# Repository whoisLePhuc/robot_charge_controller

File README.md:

# Robot Charge Controller

An ESP32-based controller for switching, monitoring, and supervising a high-power DC charging path for mobile robots. The project supports two hardware architectures that coexist in this repository and share the same project-local KiCad libraries.

> [!WARNING]
> This project targets a charging path of up to **60 VDC and 20 A**. This energy level can cause arcing, overheating, fire, equipment damage, or personal injury. Both hardware variants are prototypes under development and have not been validated for production or safety-critical use.

## Hardware Variants

| Variant | Description | Current state |
|---|---|---|
| [One-Board Design](hardware/One_Board_Design/README.md) | Relay path, sensing, auxiliary power, ESP32 control, and communications on one PCB | KiCad schematic and PCB present; engineering checks remain open |
| [Split-Board Design](hardware/Split_Board_Design/README.md) | Control Board and Relay Board connected through a controlled interface | Requirements scaffold present; KiCad projects not started |

Both variants are directories in the same repository. Branches are used for temporary changes, not as the only place where a hardware variant can be discovered.

## Design Targets

| Item | Target | Evidence status |
|---|---:|---|
| Main bus voltage | Up to 60 VDC | Project requirement |
| Continuous current | Up to 20 A | Requires electrical and thermal verification |
| Auxiliary input | 24 VDC | Project requirement |
| Controller | ESP32-WROOM-32E | Present in the One-Board Design |
| Communications | CAN, RS485, and 3.3 V UART | Present in the One-Board Design |
| PCB baseline | Two layers, nominal 1.6 mm, 2 oz finished copper on F.Cu and B.Cu | Selected baseline; fabricator stack-up and finish require review |

This project does not replace a battery charger or battery management system. Battery-chemistry charging control, cell balancing, and pack-level protection remain the responsibility of the external charger and BMS.

## Repository Structure

~~~text
robot_charge_controller/
├── README.md
├── CHANGELOG.md
├── LICENSE
├── components/
│   └── bom/                       # BOM workbook candidates and index
├── docs/
│   ├── 01-requirements/
│   ├── 02-architecture/
│   ├── 03-design/
│   ├── 04-calculations/
│   ├── 05-reviews/
│   ├── 06-verification/
│   ├── decisions/                 # Architecture decision records
│   └── workflow.md
├── firmware/
├── hardware/
│   ├── One_Board_Design/
│   ├── Split_Board_Design/
│   ├── libraries/                 # Shared KiCad symbols, footprints, and 3D models
│   └── templates/
├── manufacturing/
├── simulation/
├── test/
└── tools/
~~~

## Getting Started

1. Read the [development workflow](docs/workflow.md).
2. Select a hardware variant from the table above.
3. Review the variant README, requirements, open findings, and shared-library path rules.
4. Open a KiCad project only from its variant directory and keep `hardware/libraries/` in the repository layout.
5. Run the repository organization check:

   ~~~sh
   python tools/check_repository.py
   ~~~

6. Before any hardware gate decision, regenerate ERC/DRC reports and record the exact board revision and open findings.

## Project Evidence

- [BOM candidates](components/bom/README.md)
- [Engineering calculations](docs/04-calculations/README.md)
- [Design guides](docs/03-design/guides/README.md)
- [Architecture decisions](docs/decisions/README.md)
- [Verification records](docs/06-verification/README.md)
- [Manufacturing records](manufacturing/README.md)

## Status

| Area | State |
|---|---|
| Repository baseline | Established; both hardware variants coexist in the repository tree |
| One-Board schematic and PCB | Present; unresolved review actions remain |
| Split-Board requirements | Initial scaffold present |
| Split-Board schematic and PCB | Not started |
| Firmware | Scaffold only |
| Simulation | Scaffold only |
| Prototype verification | Not confirmed by controlled repository evidence |
| Production release | Not authorized |

## License

This repository is licensed under the [MIT License](LICENSE). Component models, third-party libraries, datasheets, and imported engineering artifacts may have separate terms that must be reviewed before redistribution.

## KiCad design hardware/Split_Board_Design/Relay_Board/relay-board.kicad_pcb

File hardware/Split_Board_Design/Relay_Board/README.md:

# Relay Board

This directory is reserved for the relay and high-current PCB of the Split-Board Design.

## Intended Scope

- DC-rated relay and the switched charging-current path.
- High-current connectors and copper paths.
- Local protection, sensing, and relay-drive functions assigned to this board by the architecture decision.
- Test access required for independent power-stage bring-up.

No KiCad project has been created. The board requirements must define normal current, fault current, transient environment, thermal limits, clearances, connectors, safe state, and the [inter-board interface contract](../interface/README.md) before schematic or PCB implementation.

The 60 VDC/20 A values are design requirements, not verified operating capability.

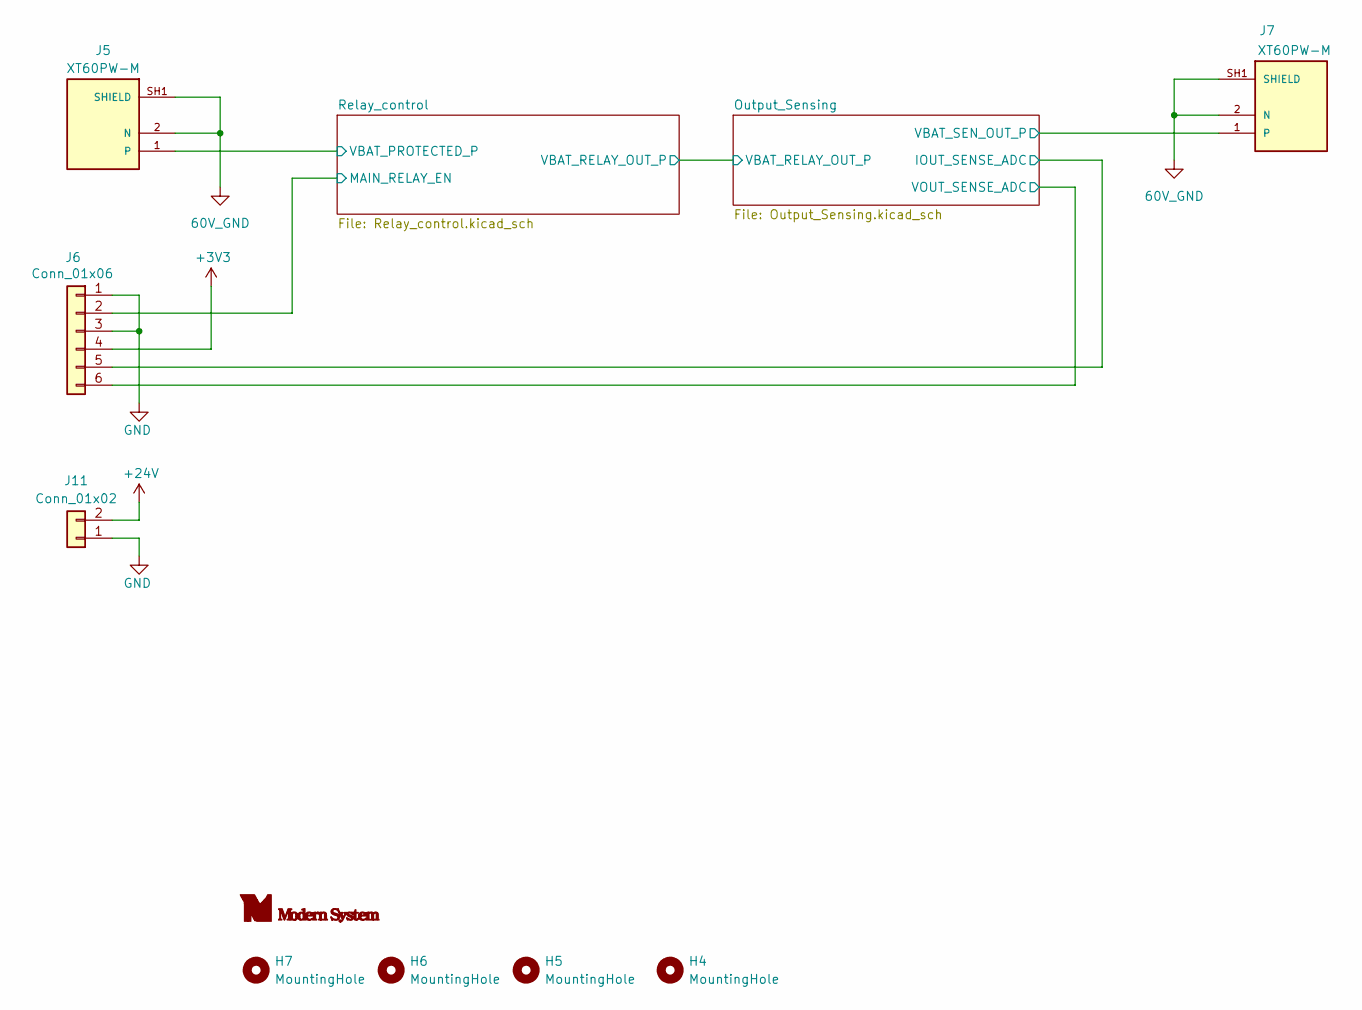
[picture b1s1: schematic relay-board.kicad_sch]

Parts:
H4, H5, H6, H7: MountingHole; MountingHole_3.2mm_M3
J5, J7: XT60PW-M; AMASS_XT60PW-M; PARTREV 1.2
J6: Conn_01x06; JST_XH_S6B-XH-A_1x06_P2.50mm_Horizontal
J11: Conn_01x02; PhoenixContact_MC_1,5_2-G-3.81_1x02_P3.81mm_Horizontal

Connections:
60V_GND: J5.2 (N), J5.SH1 (SHIELD), J5.SH2 (SHIELD), J7.2 (N), J7.SH1 (SHIELD), J7.SH2 (SHIELD); also elsewhere on the board
+3V3: J6.4; also elsewhere on the board
+24V: J11.2; also elsewhere on the board
/Output_Sensing/IOUT_SENSE_ADC: J6.5; also elsewhere on the board
/Output_Sensing/VBAT_SEN_OUT_P: J7.1; also elsewhere on the board
/Output_Sensing/VOUT_SENSE_ADC: J6.6; also elsewhere on the board
/Relay_control/MAIN_RELAY_EN: J6.2; also elsewhere on the board
/Relay_control/VBAT_PROTECTED_P: J5.1; also elsewhere on the board
GND: J6.1, J6.3, J11.1; also elsewhere on the board

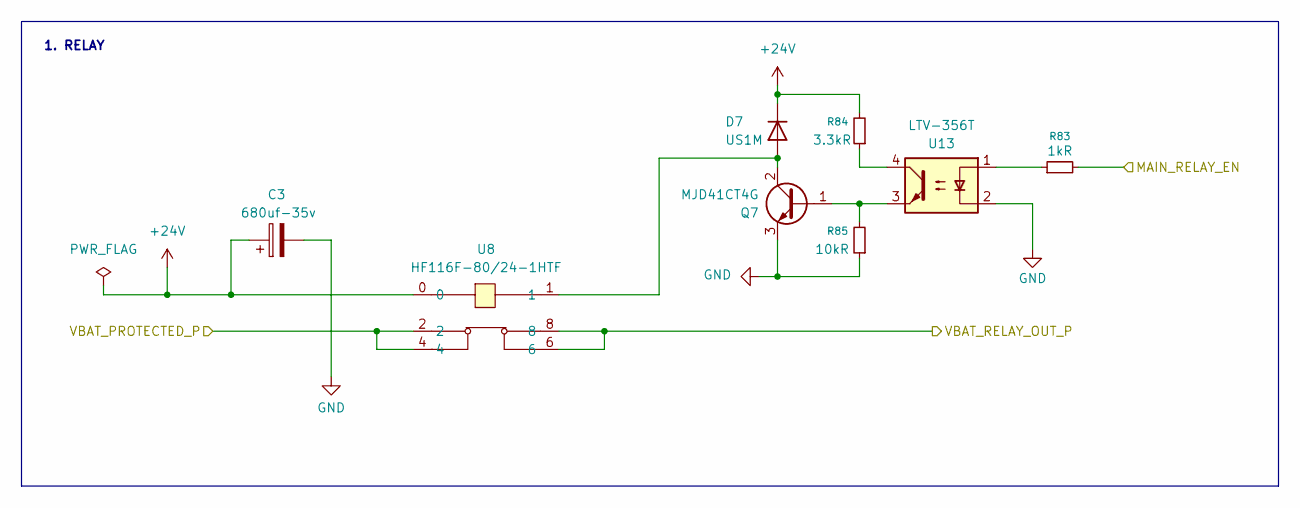
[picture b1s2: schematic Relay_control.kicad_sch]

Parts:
C3: 680uf-35v; CP_Elec_12.5x13.5_Generic_H13
D7: US1M; D_SMA
Q7: MJD41CT4G; TO-252-2
R83: 1kR; R_0805_2012Metric
R84: 3.3kR; R_0805_2012Metric
R85: 10kR; R_0805_2012Metric
U8: HF116F-80/24-1HTF; RELAY-TH_HF116F-80-XX-1HTF
U13: LTV-356T; SO-4_4.4x3.6mm_P2.54mm

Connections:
+24V: C3.1, D7.1 (K), R84.2, U8.0; also elsewhere on the board
/Output_Sensing/VBAT_RELAY_OUT_P: U8.6, U8.8; also elsewhere on the board
/Relay_control/MAIN_RELAY_EN: R83.2; also elsewhere on the board
/Relay_control/VBAT_PROTECTED_P: U8.2, U8.4; also elsewhere on the board
GND: C3.2, Q7.3 (E), R85.1, U13.2; also elsewhere on the board
unnamed: D7.2 (A), Q7.2 (C), U8.1
unnamed: Q7.1 (B), R85.2, U13.3
unnamed: R83.1, U13.1
unnamed: R84.1, U13.4

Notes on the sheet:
1. RELAY

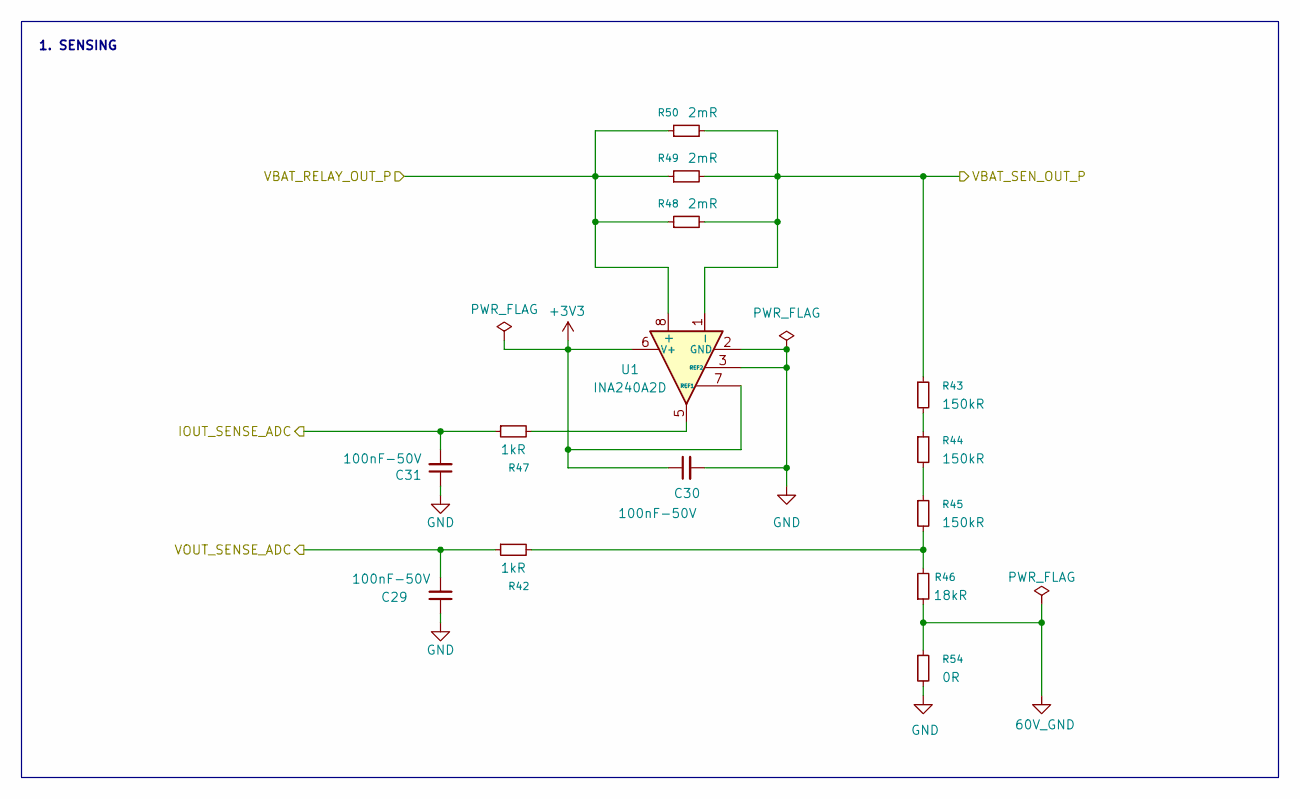
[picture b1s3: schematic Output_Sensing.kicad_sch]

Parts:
C29, C31: 100nF-50V; C_0603_1608Metric
C30: 100nF-50V; C_0805_2012Metric
R42, R47: 1kR; R_0603_1608Metric
R43, R44, R45: 150kR; R_0603_1608Metric
R46: 18kR; R_0603_1608Metric
R48, R49, R50: 2mR; R_Shunt_FOJAN_2512L_4Terminal_Kelvin_C
R54: 0R; R_1206_3216Metric
U1: INA240A2D; SOIC-8_3.9x4.9mm_P1.27mm

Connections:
60V_GND: R46.1, R54.1; also elsewhere on the board
+3V3: C30.1, U1.6 (V+), U1.7 (REF1); also elsewhere on the board
/Output_Sensing/IOUT_SENSE_ADC: C31.2, R47.1; also elsewhere on the board
/Output_Sensing/VBAT_RELAY_OUT_P: R48.1, R49.1, R50.1, U1.8 (+); also elsewhere on the board
/Output_Sensing/VBAT_SEN_OUT_P: R43.1, R48.2, R49.2, R50.2, U1.1 (-); also elsewhere on the board
/Output_Sensing/VOUT_SENSE_ADC: C29.2, R42.1; also elsewhere on the board
GND: C29.1, C30.2, C31.1, R54.2, U1.2 (GND), U1.3 (REF2), U1.4 (GND); also elsewhere on the board
unnamed: R42.2, R45.2, R46.2
unnamed: R43.2, R44.1
unnamed: R44.2, R45.1
unnamed: R47.2, U1.5

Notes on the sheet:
1. SENSING

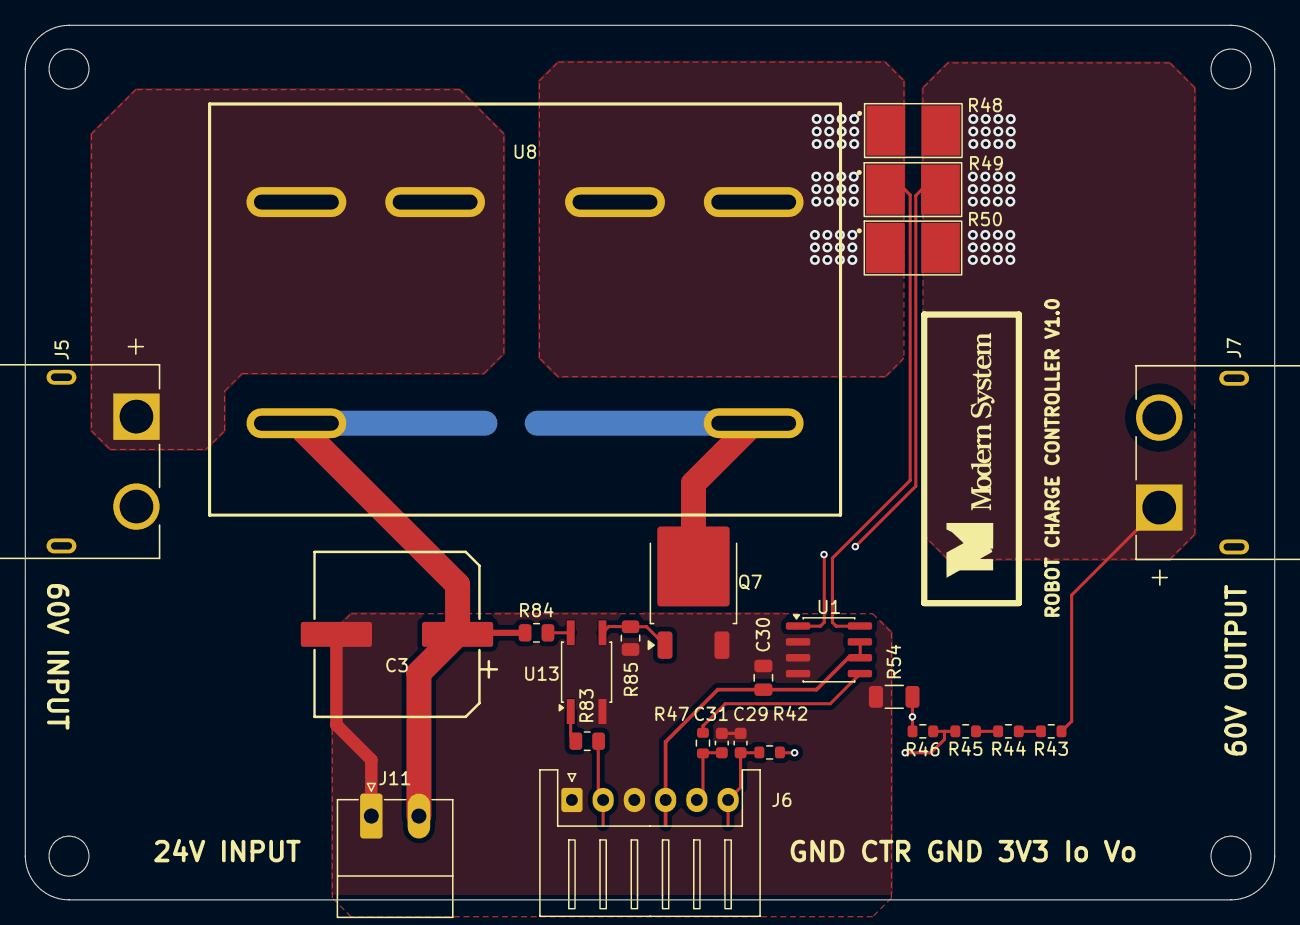
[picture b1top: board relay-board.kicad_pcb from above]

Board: 4 copper layers, 100.0 x 70.0 mm, 30 parts (1 on the bottom side), 18 nets.

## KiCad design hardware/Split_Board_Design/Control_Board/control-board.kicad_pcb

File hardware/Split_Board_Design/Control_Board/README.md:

# Control Board

This directory is reserved for the low-voltage controller PCB of the Split-Board Design.

## Intended Scope

- ESP32 supervision and state control.
- Low-voltage logic power required by the controller electronics.
- USB/programming support and diagnostic access.
- CAN, RS485, and 3.3 V UART communication interfaces.
- External low-voltage inputs and outputs assigned to this board by the interface decision.

No KiCad project has been created. Schematic capture must wait until the [inter-board interface contract](../interface/README.md) defines power, signal, reference-ground, startup, shutdown, and fault behavior.

The final allocation of sensing analog front ends, relay-coil drive, and auxiliary field outputs remains an open architecture decision.

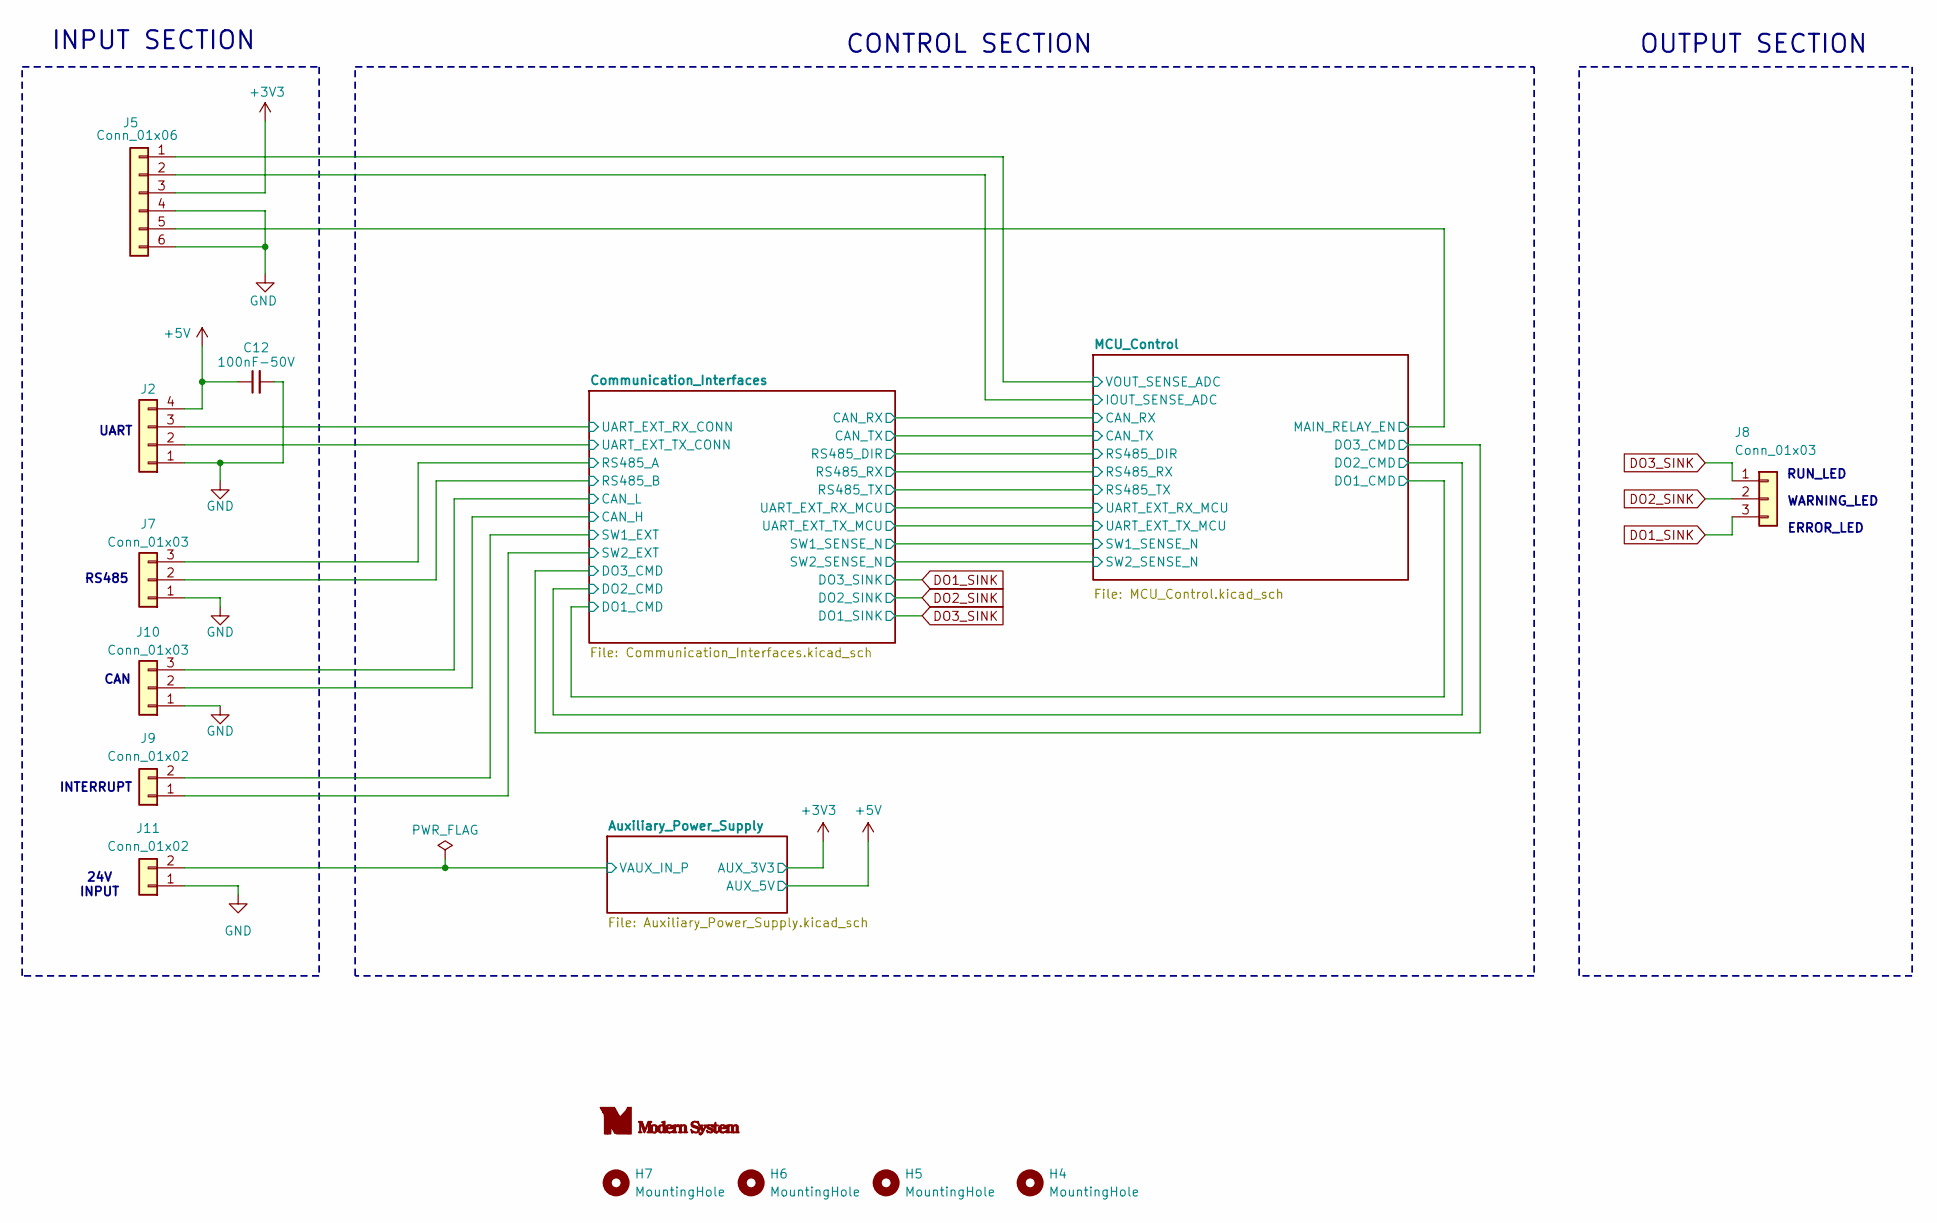
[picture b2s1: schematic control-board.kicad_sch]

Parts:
C12: 100nF-50V; C_0603_1608Metric
H4, H5, H6, H7: MountingHole; MountingHole_3.2mm_M3
J2: UART_CONN; JST_XH_S4B-XH-A-1_1x04_P2.50mm_Horizontal; MPN XH2.54-4P (bent pin)
J5: Conn_01x06; JST_XH_S6B-XH-A_1x06_P2.50mm_Horizontal
J7, J8, J10: Conn_01x03; PhoenixContact_MC_1,5_3-G-3.81_1x03_P3.81mm_Horizontal
J9, J11: Conn_01x02; PhoenixContact_MC_1,5_2-G-3.81_1x02_P3.81mm_Horizontal

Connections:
+3V3: J5.3; also elsewhere on the board
+5V: C12.1, J2.4; also elsewhere on the board
/Auxiliary_Power_Supply/VAUX_IN_P: J11.2; also elsewhere on the board
/Communication_Interfaces/CAN_H: J10.2; also elsewhere on the board
/Communication_Interfaces/CAN_L: J10.3; also elsewhere on the board
/Communication_Interfaces/RS485_A: J7.3; also elsewhere on the board
/Communication_Interfaces/RS485_B: J7.2; also elsewhere on the board
/Communication_Interfaces/SW1_EXT: J9.2; also elsewhere on the board
/Communication_Interfaces/SW2_EXT: J9.1; also elsewhere on the board
/Communication_Interfaces/UART_EXT_RX_CONN: J2.3; also elsewhere on the board
/Communication_Interfaces/UART_EXT_TX_CONN: J2.2; also elsewhere on the board
/MCU_Control/IOUT_SENSE_ADC: J5.2; also elsewhere on the board
/MCU_Control/MAIN_RELAY_EN: J5.5; also elsewhere on the board
/MCU_Control/VOUT_SENSE_ADC: J5.1; also elsewhere on the board
DO1_SINK: J8.3; also elsewhere on the board
DO2_SINK: J8.2; also elsewhere on the board
DO3_SINK: J8.1; also elsewhere on the board
GND: C12.2, J2.1, J5.4, J5.6, J7.1, J10.1, J11.1; also elsewhere on the board

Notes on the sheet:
OUTPUT SECTION
INPUT SECTION
RUN_LED
RS485
WARNING_LED
CONTROL SECTION
INTERRUPT
UART
ERROR_LED
24V INPUT
CAN

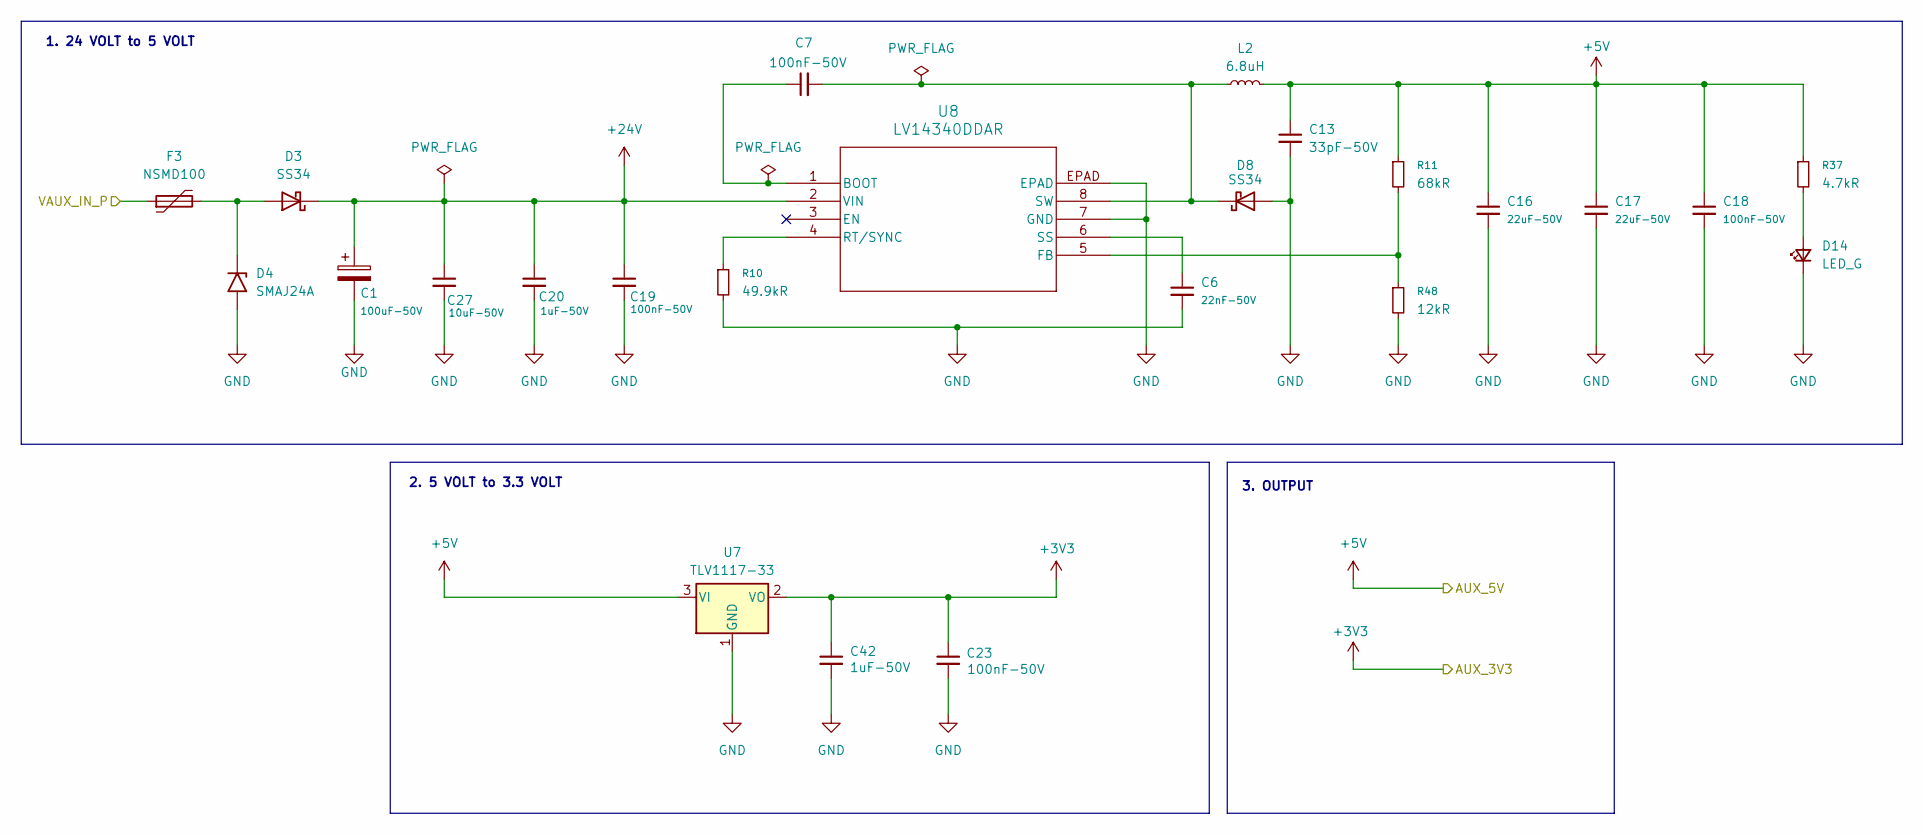
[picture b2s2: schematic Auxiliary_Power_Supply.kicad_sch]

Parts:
C1: 100uF-50V; CP_Elec_8x10.5
C6: 22nF-50V; C_0603_1608Metric
C7, C18, C19, C23: 100nF-50V; C_0603_1608Metric
C13: 33pF-50V; C_0603_1608Metric
C16, C17: 22uF-50V; C_0805_2012Metric
C20, C42: 1uF-50V; C_0603_1608Metric
C27: 10uF-50V; C_0603_1608Metric
D3, D8: SS34; D_SMA; LCSC Part C2837271
D4: SMAJ24A; D_SMA
D14: LED_G; LED_0603_1608Metric
F3: NSMD100; Fuse_1206_3216Metric; MPN nSMD100; LCSC Part C66453
L2: 6.8uH; L_Changjiang_FXL0630
R10: 49.9kR; R_0603_1608Metric
R11: 68kR; R_0603_1608Metric
R37: 4.7kR; R_0603_1608Metric
R48: 12kR; R_0603_1608Metric
U7: TLV1117-33; SOT-223-3_TabPin2
U8: LV14340DDAR; SOIC8_DDA_TEX

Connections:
+3V3: C23.1, C42.1, U7.2 (VO); also elsewhere on the board
+5V: C13.1, C16.1, C17.1, C18.1, L2.2, R11.1, R37.1, U7.3 (VI); also elsewhere on the board
+24V: C1.1, C19.1, C20.1, C27.1, D3.1 (K), U8.2 (VIN); also elsewhere on the board
/Auxiliary_Power_Supply/VAUX_IN_P: F3.1; also elsewhere on the board
GND: C1.2, C6.2, C13.2, C16.2, C17.2, C18.2, C19.2, C20.2, C23.2, C27.2, C42.2, D4.2 (A2), D8.2 (A), D14.1 (K), R10.2, R48.2, U7.1 (GND), U8.7 (GND), U8.EPAD; also elsewhere on the board
unnamed: D3.2 (A), D4.1 (A1), F3.2
unnamed: C7.2, D8.1 (K), L2.1, U8.8 (SW)
unnamed: D14.2 (A), R37.2
unnamed: C7.1, U8.1 (BOOT)
unnamed: R11.2, R48.1, U8.5 (FB)
unnamed: R10.1, U8.4 (RT/SYNC)
unnamed: C6.1, U8.6 (SS)

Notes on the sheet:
2. 5 VOLT to 3.3 VOLT
1. 24 VOLT to 5 VOLT
3. OUTPUT

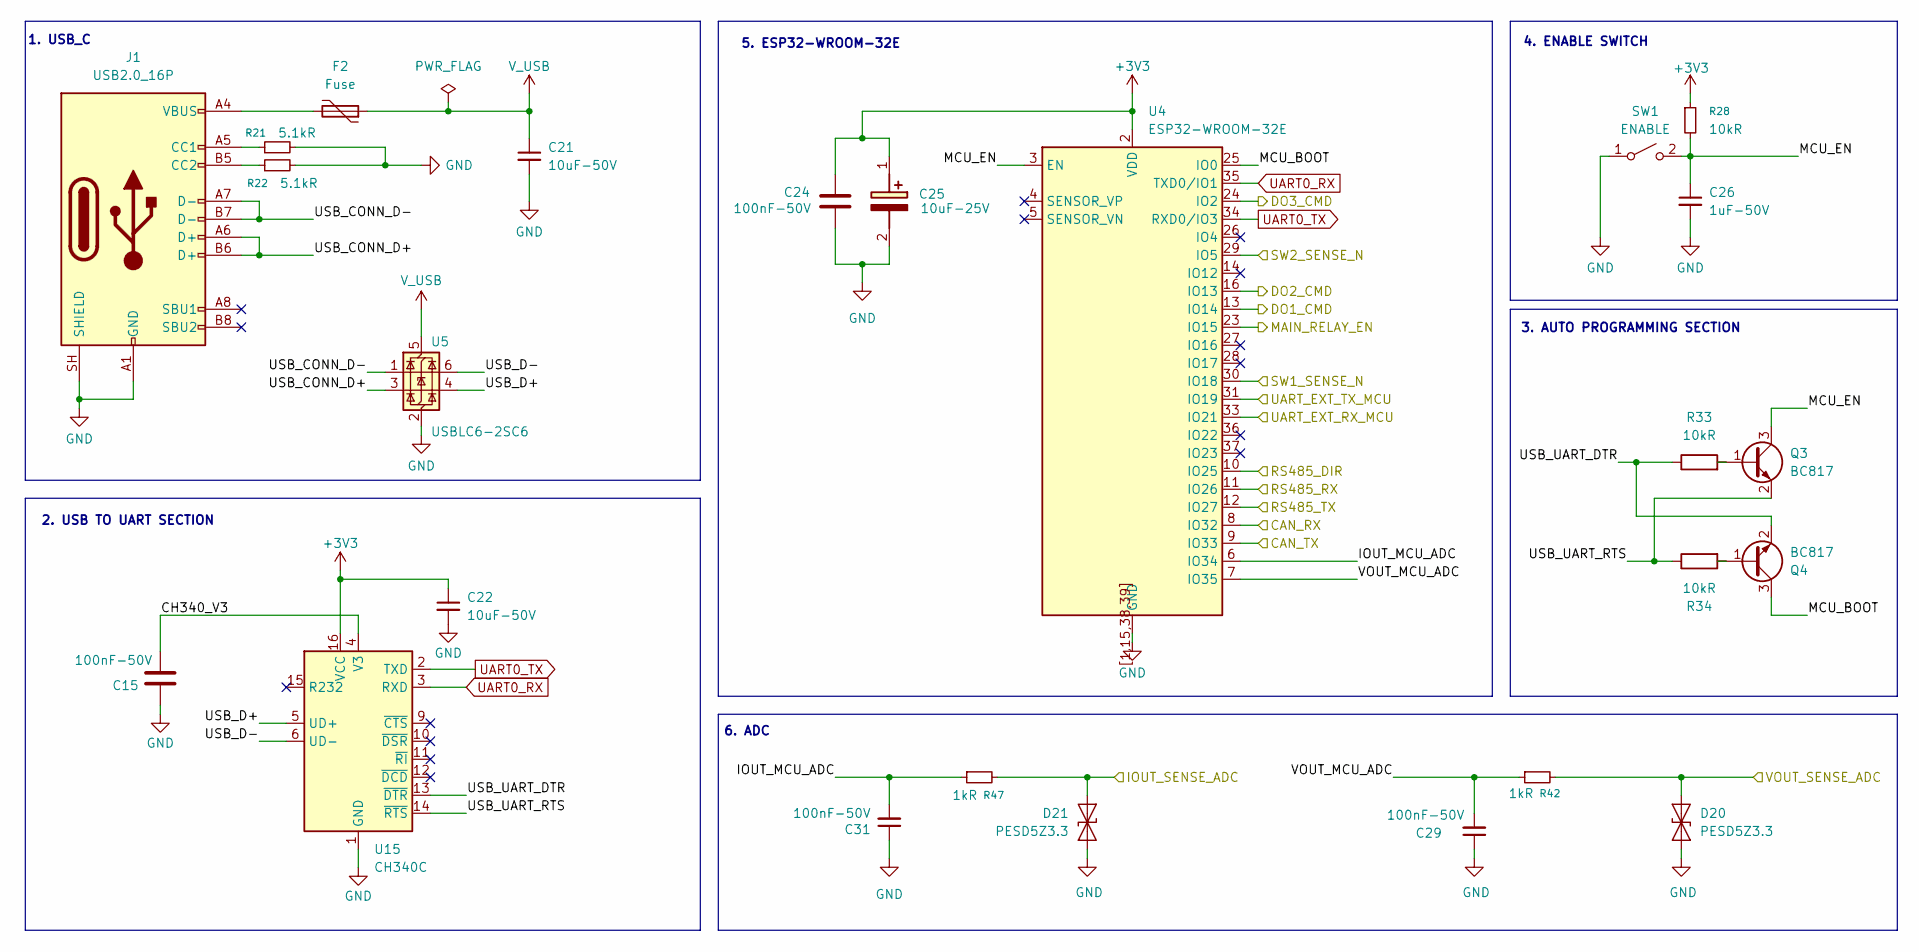
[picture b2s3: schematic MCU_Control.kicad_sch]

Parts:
C15, C24: 100nF-50V; C_0603_1608Metric; Voltage 1kV; Tolerance 100%
C21, C22: 10uF-50V; C_0603_1608Metric
C25: 10uF-25V; CP_EIA-3528-12_Kemet-T; Voltage 1kV; Tolerance 100%; Manufacturer_Part_Number T491A106K010AT7280; Mouser Part Number 80-T491A106K107280
C26: 1uF-50V; C_0603_1608Metric
C29, C31: 100nF-50V; C_0603_1608Metric
D20: PESD5Z3.3; D_SOD-523
D21: PESD5Z3.3; D_SOD-523; MPN PESD5Z3.3
F2: Fuse; Fuse_1206_3216Metric; MPN nSMD100; LCSC Part C66453
J1: USB2.0_16P; USB_C_Receptacle_GCT_USB4105-xx-A_16P_TopMnt_Horizontal; MPN USB4105-GF-A
Q3, Q4: BC817; SOT-23-3; Manufacturer_Part_Number BC817
R21, R22: 5.1kR; R_0603_1608Metric
R28, R33, R34: 10kR; R_0603_1608Metric
R42, R47: 1kR; R_0603_1608Metric
SW1: ENABLE; SW_SPST_B3U-1000P; MPN B3U-1000P; LCSC Part C231329
U4: ESP32-WROOM-32E; ESP32-WROOM-32UE; MPN ESP32-WROOM-32E
U5: USBLC6-2SC6; SOT-23-6; MPN USBLC6-2SC6; LCSC Part C7519
U15: CH340C; SOIC-16_3.9x9.9mm_P1.27mm

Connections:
+3V3: C22.1, C24.1, C25.1 (+), R28.1, U4.2 (VDD), U15.16 (VCC); also elsewhere on the board
/Communication_Interfaces/CAN_RX: U4.8 (IO32); also elsewhere on the board
/Communication_Interfaces/CAN_TX: U4.9 (IO33); also elsewhere on the board
/Communication_Interfaces/DO1_CMD: U4.13 (IO14); also elsewhere on the board
/Communication_Interfaces/DO2_CMD: U4.16 (IO13); also elsewhere on the board
/Communication_Interfaces/DO3_CMD: U4.24 (IO2); also elsewhere on the board
/Communication_Interfaces/RS485_DIR: U4.10 (IO25); also elsewhere on the board
/Communication_Interfaces/RS485_RX: U4.11 (IO26); also elsewhere on the board
/Communication_Interfaces/RS485_TX: U4.12 (IO27); also elsewhere on the board
/Communication_Interfaces/SW1_SENSE_N: U4.30 (IO18); also elsewhere on the board
/Communication_Interfaces/SW2_SENSE_N: U4.29 (IO5); also elsewhere on the board
/Communication_Interfaces/UART_EXT_RX_MCU: U4.33 (IO21); also elsewhere on the board
/Communication_Interfaces/UART_EXT_TX_MCU: U4.31 (IO19); also elsewhere on the board
/MCU_Control/CH340_V3: C15.1, U15.4 (V3)
/MCU_Control/IOUT_MCU_ADC: C31.2, R47.1, U4.6 (IO34)
/MCU_Control/IOUT_SENSE_ADC: D21.1 (A1), R47.2; also elsewhere on the board
/MCU_Control/MAIN_RELAY_EN: U4.23 (IO15); also elsewhere on the board
/MCU_Control/MCU_BOOT: Q4.3 (C), U4.25 (IO0)
/MCU_Control/MCU_EN: C26.1, Q3.3 (C), R28.2, SW1.2 (B), U4.3 (EN)
/MCU_Control/USB_CONN_D+: J1.A6 (D+), J1.B6 (D+), U5.3 (I/O2)
/MCU_Control/USB_CONN_D-: J1.A7 (D-), J1.B7 (D-), U5.1 (I/O1)
/MCU_Control/USB_D+: U5.4 (I/O2), U15.5 (UD+)
/MCU_Control/USB_D-: U5.6 (I/O1), U15.6 (UD-)
/MCU_Control/USB_UART_DTR: Q4.2 (E), R33.1, U15.13 (~DTR)
/MCU_Control/USB_UART_RTS: Q3.2 (E), R34.1, U15.14 (~RTS)
/MCU_Control/VOUT_MCU_ADC: C29.2, R42.1, U4.7 (IO35)
/MCU_Control/VOUT_SENSE_ADC: D20.1 (A1), R42.2; also elsewhere on the board
GND: C15.2, C21.2, C22.2, C24.2, C25.2 (-), C26.2, C29.1, C31.1, D20.2 (A2), D21.2 (A2), J1.A1 (GND), J1.A12 (GND), J1.B1 (GND), J1.B12 (GND), J1.SH (SHIELD), R21.2, R22.2, SW1.1 (A), U4.1 (GND), U4.15 (GND), U4.38 (GND), U4.39 (GND), U4.[1,15,38,39] (GND), U5.2 (GND), U15.1 (GND); also elsewhere on the board
unnamed: F2.2, J1.A4 (VBUS), J1.A9 (VBUS), J1.B4 (VBUS), J1.B9 (VBUS)
unnamed: J1.A5 (CC1), R21.1
unnamed: J1.B5 (CC2), R22.1
unnamed: Q3.1 (B), R33.2
unnamed: Q4.1 (B), R34.2
UART0_RX: U4.35 (TXD0/IO1), U15.3 (RXD)
UART0_TX: U4.34 (RXD0/IO3), U15.2 (TXD)
V_USB: C21.1, F2.1, U5.5 (VBUS)

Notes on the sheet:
2. USB TO UART SECTION
5. ESP32-WROOM-32E
1. USB_C
6. ADC
3. AUTO PROGRAMMING SECTION
4. ENABLE SWITCH

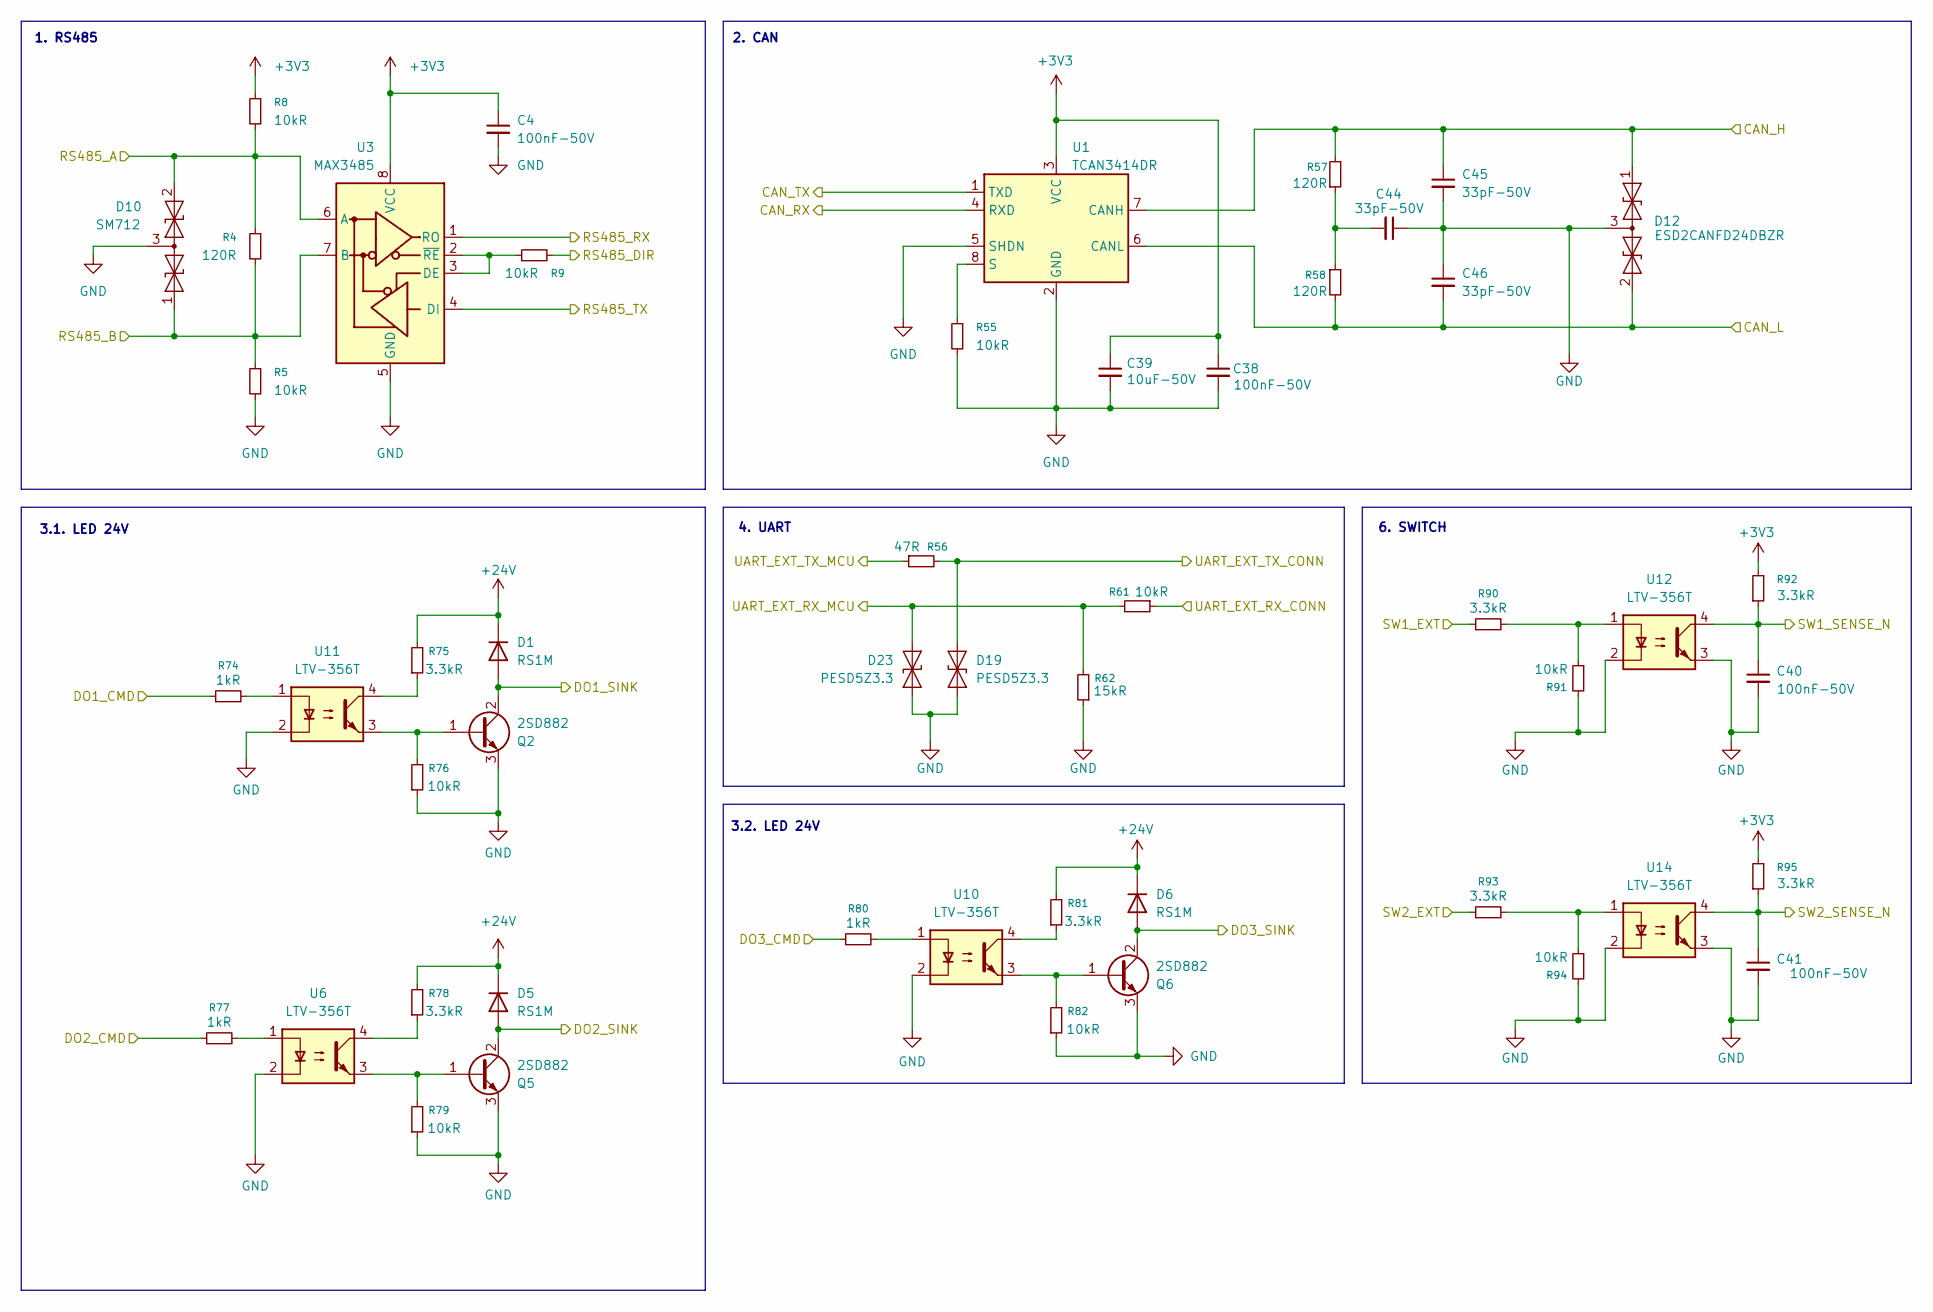
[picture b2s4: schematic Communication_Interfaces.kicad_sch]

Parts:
C4, C38, C40, C41: 100nF-50V; C_0603_1608Metric
C39: 10uF-50V; C_0603_1608Metric
C44, C45, C46: 33pF-50V; C_0603_1608Metric
D1, D5, D6: RS1M; D_SOD-123; MPN RS1M
D10: SM712; SOT-23; MPN SM712
D12: ESD2CANFD24DBZR; SOT-23; MPN ESD2CANFD24DBZR
D19, D23: PESD5Z3.3; D_SOD-523
Q2, Q5, Q6: 2SD882; SOT-89-3
R4, R57, R58: 120R; R_0603_1608Metric
R5, R8, R9, R55, R61, R82, R91, R94: 10kR; R_0603_1608Metric
R56: 47R; R_0603_1608Metric
R62: 15kR; R_0603_1608Metric
R74, R77, R80: 1kR; R_0603_1608Metric
R75, R78, R81, R90, R92, R93, R95: 3.3kR; R_0603_1608Metric
R76, R79: 10kR; R_0805_2012Metric
U1: TCAN3414DR; SOIC-8_3.9x4.9mm_P1.27mm
U3: MAX3485; SOIC-8_3.9x4.9mm_P1.27mm; MPN MAX3485CSA; LCSC Part C18148
U6, U10, U11, U12, U14: LTV-356T; SO-4_4.4x3.6mm_P2.54mm

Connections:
+3V3: C4.1, C38.1, C39.1, R8.1, R92.2, R95.2, U1.3 (VCC), U3.8 (VCC); also elsewhere on the board
+24V: D1.1 (K), D5.1 (K), D6.1 (K), R75.2, R78.2, R81.2; also elsewhere on the board
/Communication_Interfaces/CAN_H: C45.1, D12.1 (A1), R57.2, U1.7 (CANH); also elsewhere on the board
/Communication_Interfaces/CAN_L: C46.2, D12.2 (A2), R58.2, U1.6 (CANL); also elsewhere on the board
/Communication_Interfaces/CAN_RX: U1.4 (RXD); also elsewhere on the board
/Communication_Interfaces/CAN_TX: U1.1 (TXD); also elsewhere on the board
/Communication_Interfaces/DO1_CMD: R74.1; also elsewhere on the board
/Communication_Interfaces/DO2_CMD: R77.1; also elsewhere on the board
/Communication_Interfaces/DO3_CMD: R80.1; also elsewhere on the board
/Communication_Interfaces/RS485_A: D10.2 (A2), R4.1, R8.2, U3.6 (A); also elsewhere on the board
/Communication_Interfaces/RS485_B: D10.1 (A1), R4.2, R5.1, U3.7 (B); also elsewhere on the board
/Communication_Interfaces/RS485_DIR: R9.2; also elsewhere on the board
/Communication_Interfaces/RS485_RX: U3.1 (RO); also elsewhere on the board
/Communication_Interfaces/RS485_TX: U3.4 (DI); also elsewhere on the board
/Communication_Interfaces/SW1_EXT: R90.1; also elsewhere on the board
/Communication_Interfaces/SW1_SENSE_N: C40.1, R92.1, U12.4; also elsewhere on the board
/Communication_Interfaces/SW2_EXT: R93.1; also elsewhere on the board
/Communication_Interfaces/SW2_SENSE_N: C41.1, R95.1, U14.4; also elsewhere on the board
/Communication_Interfaces/UART_EXT_RX_CONN: R61.1; also elsewhere on the board
/Communication_Interfaces/UART_EXT_RX_MCU: D23.1 (A1), R61.2, R62.2; also elsewhere on the board
/Communication_Interfaces/UART_EXT_TX_CONN: D19.1 (A1), R56.2; also elsewhere on the board
/Communication_Interfaces/UART_EXT_TX_MCU: R56.1; also elsewhere on the board
DO1_SINK: D6.2 (A), Q6.2 (C); also elsewhere on the board
DO2_SINK: D5.2 (A), Q5.2 (C); also elsewhere on the board
DO3_SINK: D1.2 (A), Q2.2 (C); also elsewhere on the board
GND: C4.2, C38.2, C39.2, C40.2, C41.2, C44.1, C45.2, C46.1, D10.3 (common), D12.3 (common), D19.2 (A2), D23.2 (A2), Q2.3 (E), Q5.3 (E), Q6.3 (E), R5.2, R55.2, R62.1, R76.1, R79.1, R82.1, R91.2, R94.2, U1.2 (GND), U1.5 (SHDN), U3.5 (GND), U6.2, U10.2, U11.2, U12.2, U12.3, U14.2, U14.3; also elsewhere on the board
unnamed: C44.2, R57.1, R58.1
unnamed: Q2.1 (B), R76.2, U11.3
unnamed: Q5.1 (B), R79.2, U6.3
unnamed: Q6.1 (B), R82.2, U10.3
unnamed: R74.2, U11.1
unnamed: R75.1, U11.4
unnamed: R77.2, U6.1
unnamed: R78.1, U6.4
unnamed: R80.2, U10.1
unnamed: R81.1, U10.4
unnamed: R90.2, R91.1, U12.1
unnamed: R93.2, R94.1, U14.1
unnamed: R55.1, U1.8 (S)
unnamed: R9.1, U3.2 (~RE), U3.3 (DE)

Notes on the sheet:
4. UART
3.1. LED 24V
6. SWITCH
1. RS485
3.2. LED 24V
2. CAN
